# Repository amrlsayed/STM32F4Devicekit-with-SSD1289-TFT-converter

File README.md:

# STM32F4Devicekit-with-SSD1289-TFT-converter

Eagle files for a connection board between the deviceKit and the ssd1289 , just a plug and play , without a lot of cabling.

<br />This work is licensed under a <a rel="license" href="http://creativecommons.org/licenses/by-sa/4.0/">Creative Commons Attribution-ShareAlike 4.0 International License</a>.

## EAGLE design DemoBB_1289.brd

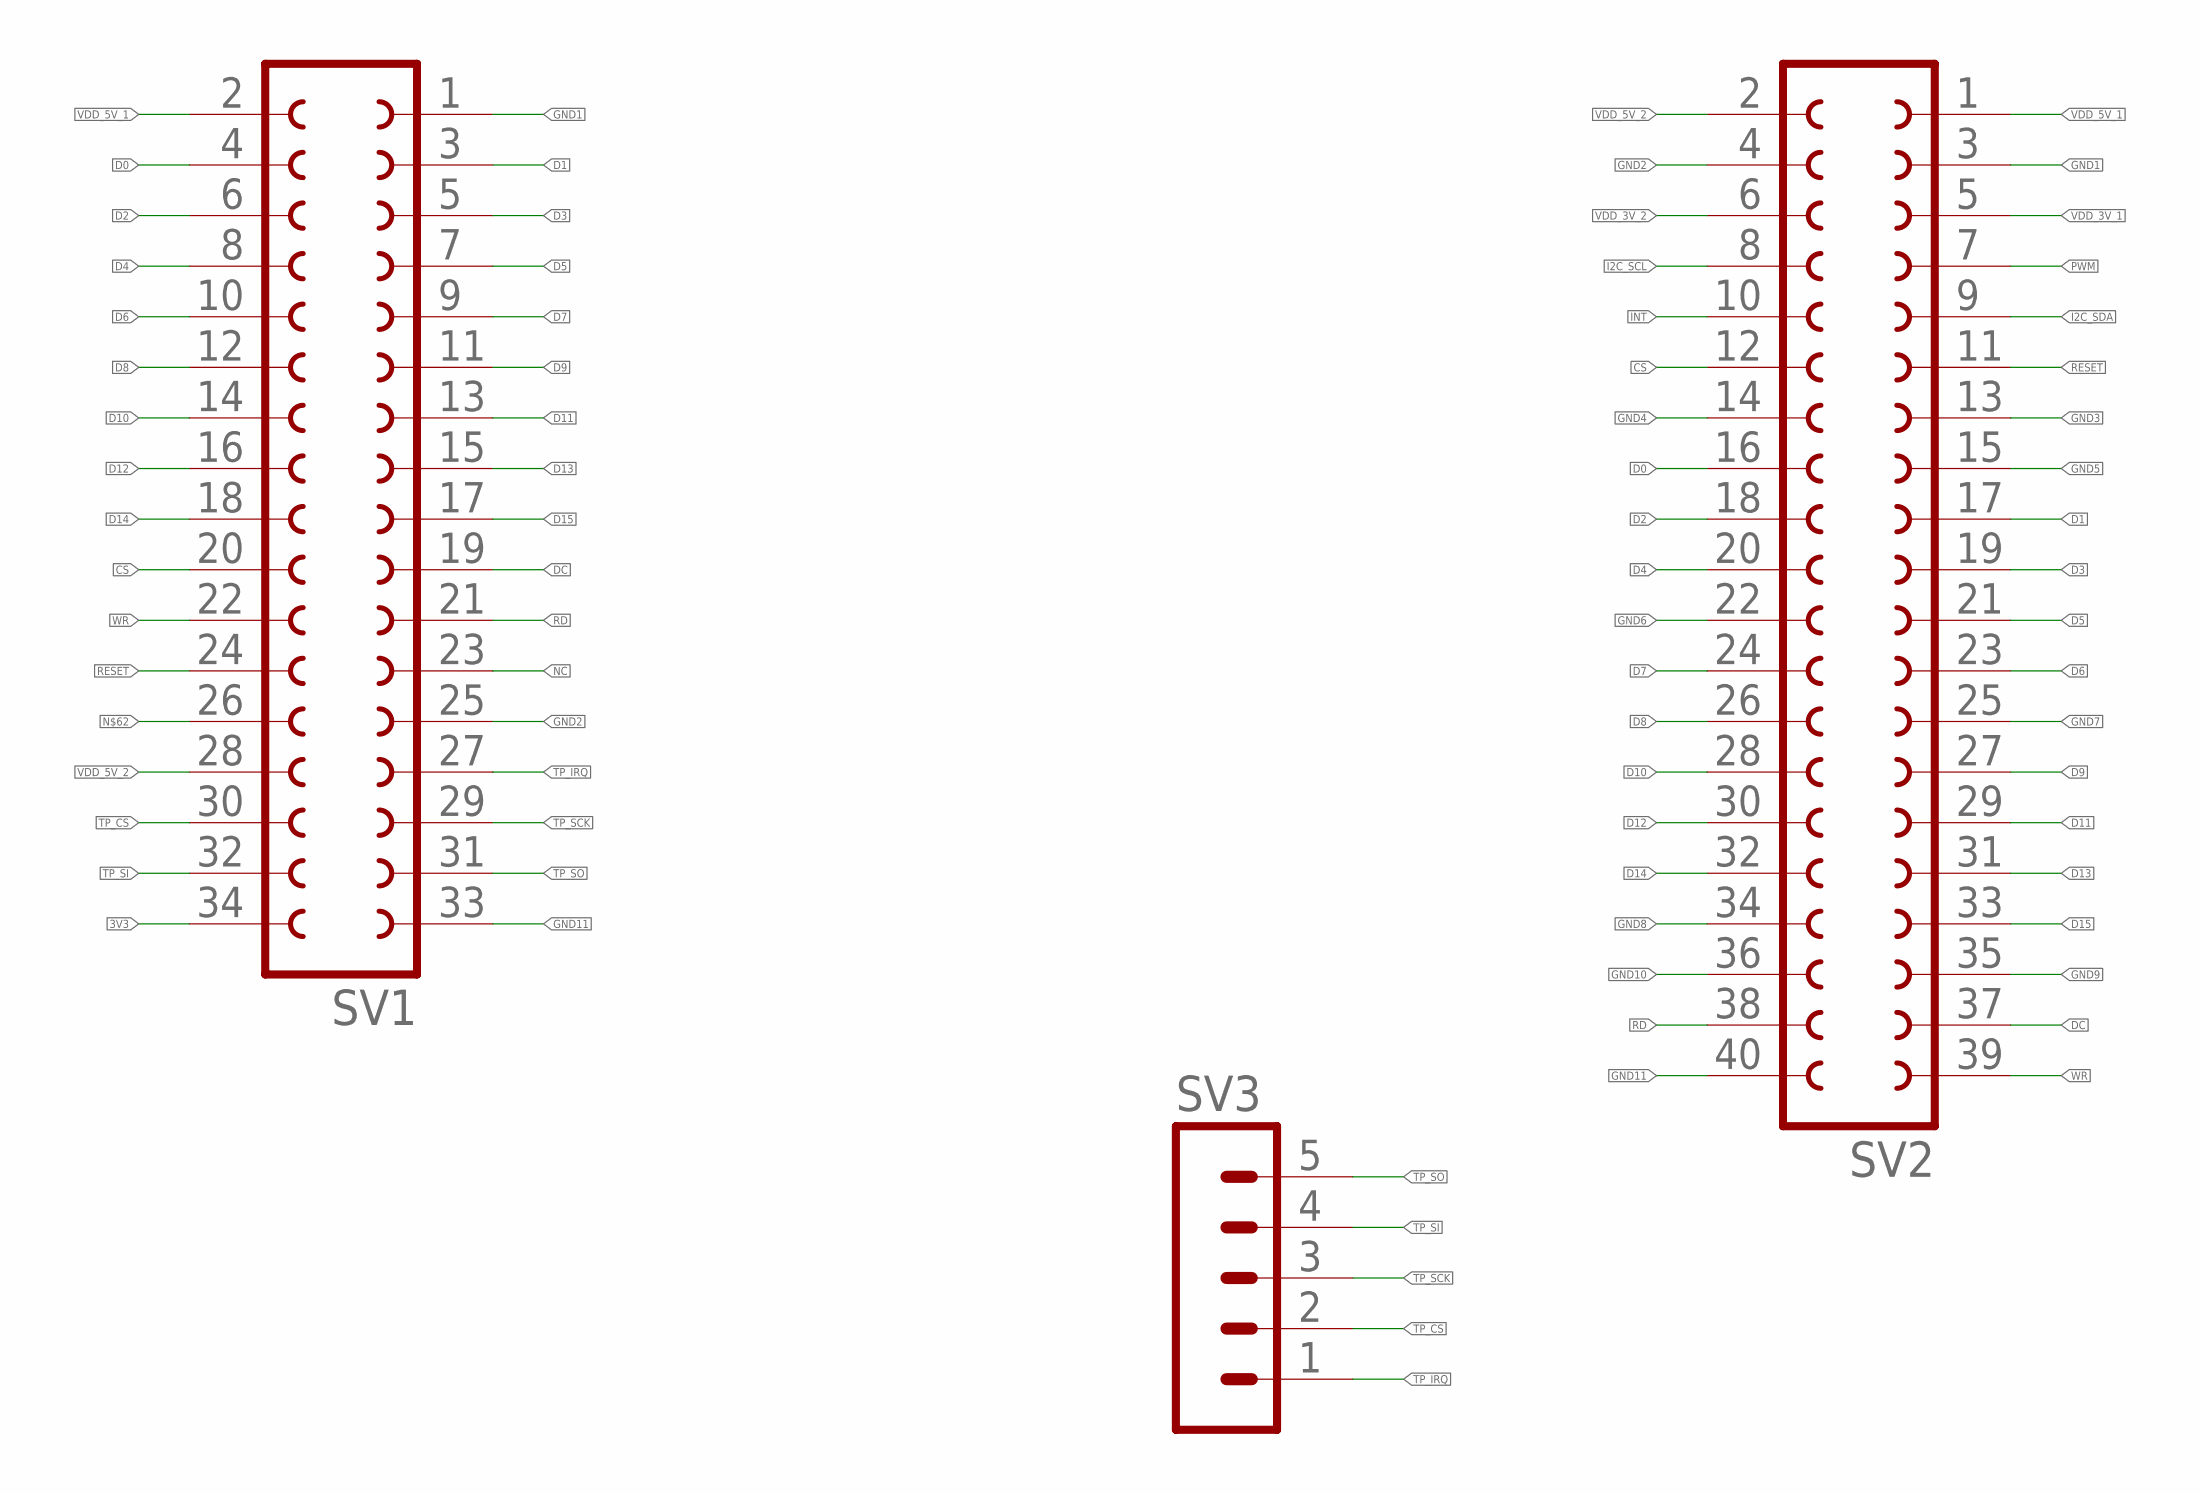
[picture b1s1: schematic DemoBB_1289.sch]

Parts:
SV1: FE17-2
SV2: FE20-2
SV3: MA05-1

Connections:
3V3: SV1.34
CS: SV1.20, SV2.12
D0: SV1.4, SV2.16
D1: SV1.3, SV2.17
D2: SV1.6, SV2.18
D3: SV1.5, SV2.19
D4: SV1.8, SV2.20
D5: SV1.7, SV2.21
D6: SV1.10, SV2.23
D7: SV1.9, SV2.24
D8: SV1.12, SV2.26
D9: SV1.11, SV2.27
D10: SV1.14, SV2.28
D11: SV1.13, SV2.29
D12: SV1.16, SV2.30
D13: SV1.15, SV2.31
D14: SV1.18, SV2.32
D15: SV1.17, SV2.33
DC: SV1.19, SV2.37
GND1: SV1.1, SV2.3
GND2: SV1.25, SV2.4
GND3: SV2.13
GND4: SV2.14
GND5: SV2.15
GND6: SV2.22
GND7: SV2.25
GND8: SV2.34
GND9: SV2.35
GND10: SV2.36
GND11: SV1.33, SV2.40
I2C_SCL: SV2.8
I2C_SDA: SV2.9
INT: SV2.10
NC: SV1.23
PWM: SV2.7
RD: SV1.21, SV2.38
RESET: SV1.24, SV2.11
TP_CS: SV1.30, SV3.2
TP_IRQ: SV1.27, SV3.1
TP_SCK: SV1.29, SV3.3
TP_SI: SV1.32, SV3.4
TP_SO: SV1.31, SV3.5
VDD_3V_1: SV2.5
VDD_3V_2: SV2.6
VDD_5V_1: SV1.2, SV2.1
VDD_5V_2: SV1.28, SV2.2
WR: SV1.22, SV2.39

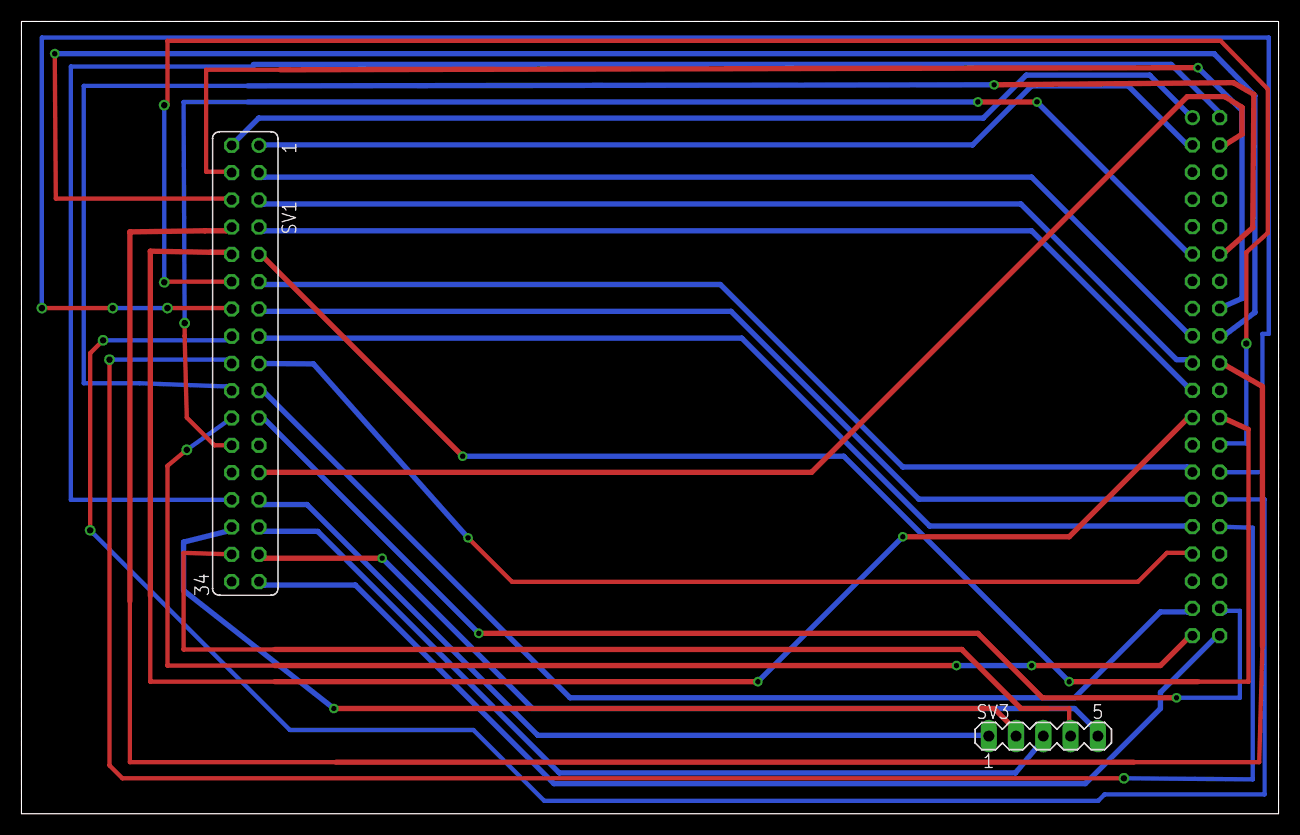
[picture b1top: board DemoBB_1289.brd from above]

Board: 2 copper layers, 117.1 x 73.8 mm, 3 parts (1 on the bottom side), 31 nets.
